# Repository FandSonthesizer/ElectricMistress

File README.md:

# ElectricMistress
This is the F&S version of this classic flanger effect. We based our PCB on the schematics from Thomeeque's EM3207.
Sounds really nice and is reasonable easy to build, check out our demo on youtube https://www.youtube.com/watch?v=bW4K1UdQq3Q

How does it work?
The mn3207 does contain a memory of 1024 steps, the 'bucket brigade'. The analog signal goes in, moves through the 'brigade' and goes to the output stage.
The faster the chip is clocked, the shorter the delay time is and vice versa. 
The clock is generated by a VCO around the LM311, then it is converted to the bi-phase clock signal the BBD chip needs. The VCO itself is modulated by the LFO consisting of U3 a,b,c. The clock rate varies from around 100kHz to a couple of hundred kHz. U1a boosts the input signal and U1b takes care of the feedback mix. Q1 is the output driver.

Fun fact: the clock driver cd4049 can be substituted by a cd4050 chip.

We have included a tiff file that you can print, cut out and fold around a 1590bb enclosure to let you know where to drill the holes.

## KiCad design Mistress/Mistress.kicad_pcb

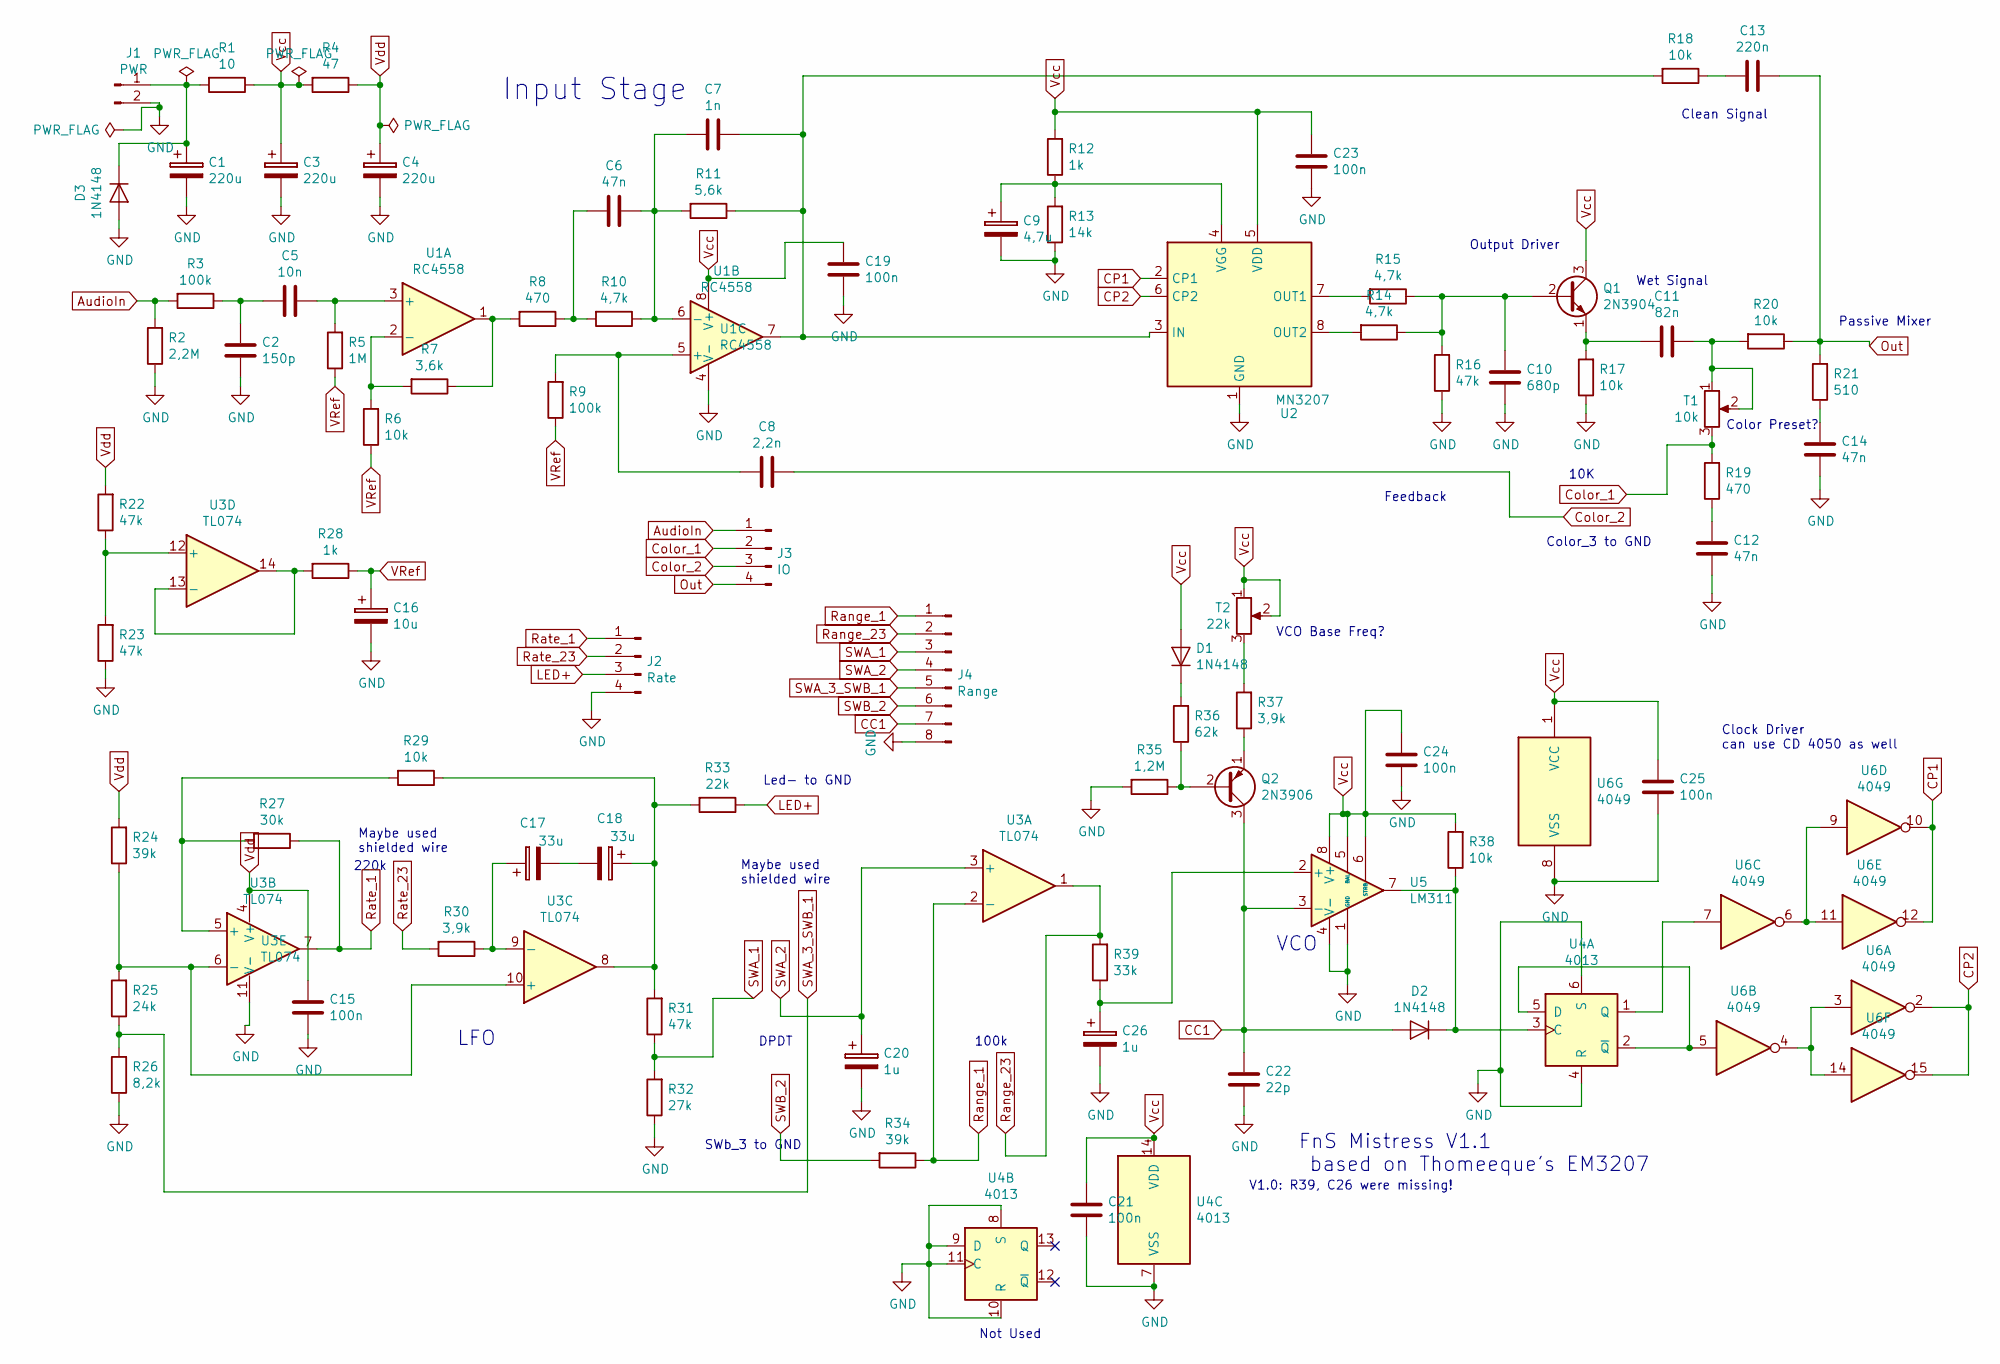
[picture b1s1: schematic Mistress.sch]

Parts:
C1, C3, C4: 220u; Elko_D6.3mm_P2.50mm
C2: 150p; Kondensator_Keramik
C5: 10n; Kondensator_Keramik
C6, C12, C14: 47n; Kondensator_Keramik
C7: 1n; Kondensator_Keramik
C8: 2,2n; Kondensator_Keramik
C9: 4,7u; Elko_D6.3mm_P2.50mm
C10: 680p; Kondensator_Keramik
C11: 82n; Kondensator_Keramik
C13: 220n; Kondensator_Keramik
C15, C19, C21, C23, C24, C25: 100n; Kondensator_Keramik
C16: 10u; Elko_D6.3mm_P2.50mm
C17, C18: 33u; Elko_D6.3mm_P2.50mm
C20, C26: 1u; Elko_D6.3mm_P2.50mm
C22: 22p; Kondensator_Keramik
D1, D2, D3: 1N4148; Diode_Horizontal
J1: PWR; Stift_x02
J2: Rate; PinHeader_1x04_P2.54mm_Vertical_NIK
J3: IO; PinHeader_1x04_P2.54mm_Vertical_NIK
J4: Range; PinHeader_1x08_P2.54mm_Vertical_Nik
Q1: 2N3904; TO-92_Wide_NIK
Q2: 2N3906; TO-92_Wide_NIK
R1: 10; Widerstand_liegend
R2: 2,2M; Widerstand_liegend
R3, R9: 100k; Widerstand_liegend
R4: 47; Widerstand_liegend
R5: 1M; Widerstand_liegend
R6, R17, R18, R20, R29, R38: 10k; Widerstand_liegend
R7: 3,6k; Widerstand_liegend
R8, R19: 470; Widerstand_liegend
R10, R14, R15: 4,7k; Widerstand_liegend
R11: 5,6k; Widerstand_liegend
R12, R28: 1k; Widerstand_liegend
R13: 14k; Widerstand_liegend
R16, R22, R23, R31: 47k; Widerstand_liegend
R21: 510; Widerstand_liegend
R24, R34: 39k; Widerstand_liegend
R25: 24k; Widerstand_liegend
R26: 8,2k; Widerstand_liegend
R27: 30k; Widerstand_liegend
R30, R37: 3,9k; Widerstand_liegend
R32: 27k; Widerstand_liegend
R33: 22k; Widerstand_liegend
R35: 1,2M; Widerstand_liegend
R36: 62k; Widerstand_liegend
R39: 33k; Widerstand_liegend
T1: 10k; Trimmer_Vertical
T2: 22k; Trimmer_Vertical
U1: RC4558; DIP-8_W7.62mm_Socket_LongPads
U2: MN3207; DIP-8_W7.62mm_Socket_LongPads
U3: TL074; DIP-14_W7.62mm_Socket_LongPads
U4: 4013; DIP-14_W7.62mm_Socket_LongPads
U5: LM311; DIP-8_W7.62mm_Socket_LongPads
U6: 4049; DIP-16_W7.62mm_Socket_LongPads

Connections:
AudioIn: J3.1, R2.2, R3.2
CC1: C22.1, D2.2 (A), J4.7, Q2.3 (C), U5.3 (-)
CP1: U2.2 (CP1), U6.10, U6.12
CP2: U2.6 (CP2), U6.2, U6.15
Color_1: J3.2, R19.2, T1.3
Color_2: C8.1, J3.3
GND: C1.2, C2.2, C3.2, C4.2, C9.2, C10.2, C12.1, C14.1, C15.2, C16.2, C19.2, C20.2, C21.2, C22.2, C23.2, C24.2, C25.2, C26.2, D3.2 (A), J1.2, J2.4, J4.8, R2.1, R13.1, R16.1, R17.1, R23.1, R26.1, R32.1, R35.2, U1.4 (V-), U2.1 (GND), U3.11 (V-), U4.4 (R), U4.6 (S), U4.7 (VSS), U4.8 (S), U4.9 (D), U4.10 (R), U4.11 (C), U5.1 (GND), U5.4 (V-), U6.8 (VSS)
LED+: J2.3, R33.1
unnamed: C1.1, D3.1 (K), J1.1, R1.2
unnamed: C2.1, C5.2, R3.1
unnamed: C5.1, R5.2, U1.3 (+)
unnamed: C6.1, C7.2, R10.1, R11.2, U1.6 (-)
unnamed: C6.2, R8.1, R10.2
unnamed: C7.1, R11.1, R18.2, U1.7, U2.3 (IN)
unnamed: C8.2, R9.2, U1.5 (+)
unnamed: C9.1, R12.1, R13.2, U2.4 (VGG)
unnamed: C10.1, Q1.2 (B), R14.1, R15.1, R16.2
unnamed: C11.1, R20.2, T1.1, T1.2
unnamed: C11.2, Q1.1 (E), R17.2
unnamed: C12.2, R19.1
unnamed: C13.2, R18.1
unnamed: C14.2, R21.1
unnamed: C17.1, R30.1, U3.9 (-)
unnamed: C17.2, C18.2
unnamed: C18.1, R29.1, R31.2, R33.2, U3.8
unnamed: C26.1, R39.1, U5.2 (+)
unnamed: D1.1 (K), R36.2
unnamed: D2.1 (K), R38.1, U4.3 (C), U5.7
unnamed: Q2.1 (E), R37.1
unnamed: Q2.2 (B), R35.1, R36.1
unnamed: R6.2, R7.2, U1.2 (-)
unnamed: R7.1, R8.2, U1.1
unnamed: R14.2, U2.8 (OUT2)
unnamed: R15.2, U2.7 (OUT1)
unnamed: R22.1, R23.2, U3.12 (+)
unnamed: R24.1, R25.2, U3.6 (-), U3.10 (+)
unnamed: R27.2, R29.2, U3.5 (+)
unnamed: R28.2, U3.13 (-), U3.14
unnamed: R37.2, T2.3
unnamed: U4.1 (Q), U6.7
unnamed: U4.2 (~Q), U4.5 (D), U6.5
unnamed: U6.6, U6.9, U6.11
unnamed: U6.3, U6.4, U6.14
Out: C13.1, J3.4, R20.1, R21.2
Range_1: J4.1, R34.1, U3.2 (-)
Range_23: J4.2, R39.2, U3.1
Rate_1: J2.1, R27.1, U3.7
Rate_23: J2.2, R30.2
SWA_1: J4.3, R31.1, R32.2
SWA_2: C20.1, J4.4, U3.3 (+)
SWA_3_SWB_1: J4.5, R25.1, R26.2
SWB_2: J4.6, R34.2
VRef: C16.1, R5.1, R6.1, R9.1, R28.1
Vcc: C3.1, C19.1, C21.1, C23.1, C24.1, C25.1, D1.2 (A), Q1.3 (C), R1.1, R4.2, R12.2, R38.2, T2.1, T2.2, U1.8 (V+), U2.5 (VDD), U4.14 (VDD), U5.5 (BAL), U5.6 (STRB), U5.8 (V+), U6.1 (VCC)
Vdd: C4.1, C15.1, R4.1, R22.2, R24.2, U3.4 (V+)

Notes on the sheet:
220k
DPDT
100k
Color_3 to GND
10K
SWb_3 to GND
VCO Base Freq?
Color Preset?
FnS Mistress V1.1 based on Thomeeque's EM3207
Clock Driver can use CD 4050 as well
Not Used
VCO
LFO
Input Stage
Output Driver
Clean Signal
Wet Signal
Passive Mixer
Feedback
Maybe used shielded wire
Led- to GND
V1.0: R39, C26 were missing!

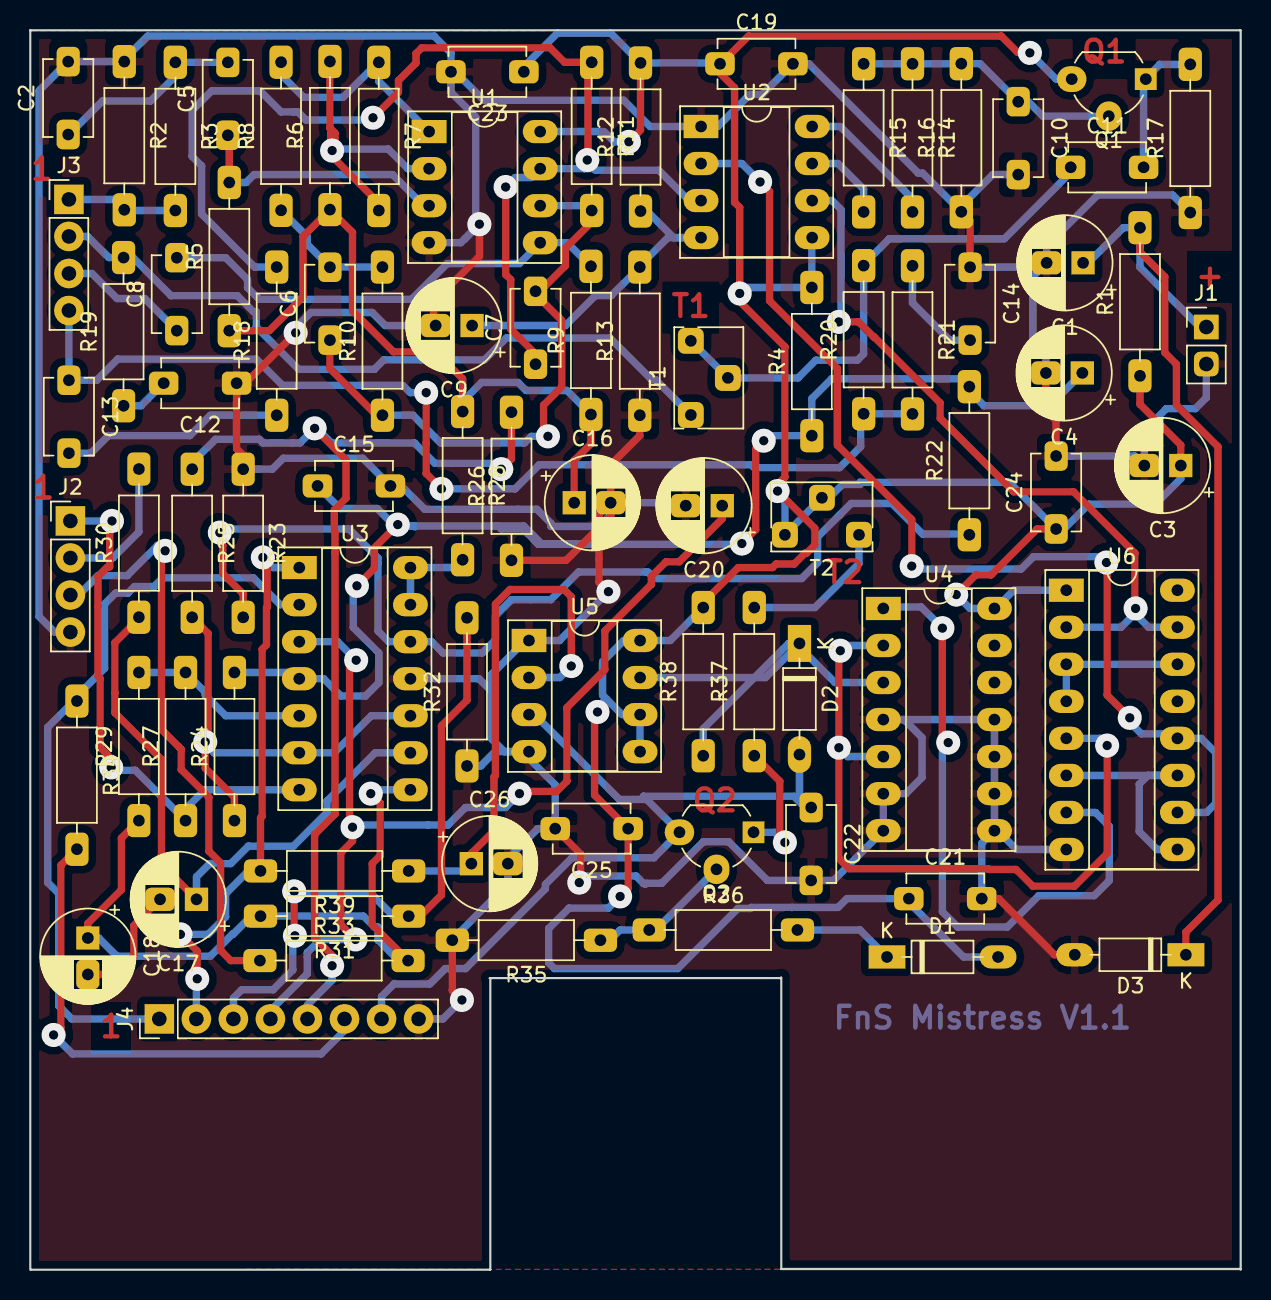
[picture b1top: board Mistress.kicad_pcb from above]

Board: 2 copper layers, 83.0 x 85.0 mm, 82 parts (0 on the bottom side), 55 nets.

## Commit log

2020-10-21 Create LICENSE
